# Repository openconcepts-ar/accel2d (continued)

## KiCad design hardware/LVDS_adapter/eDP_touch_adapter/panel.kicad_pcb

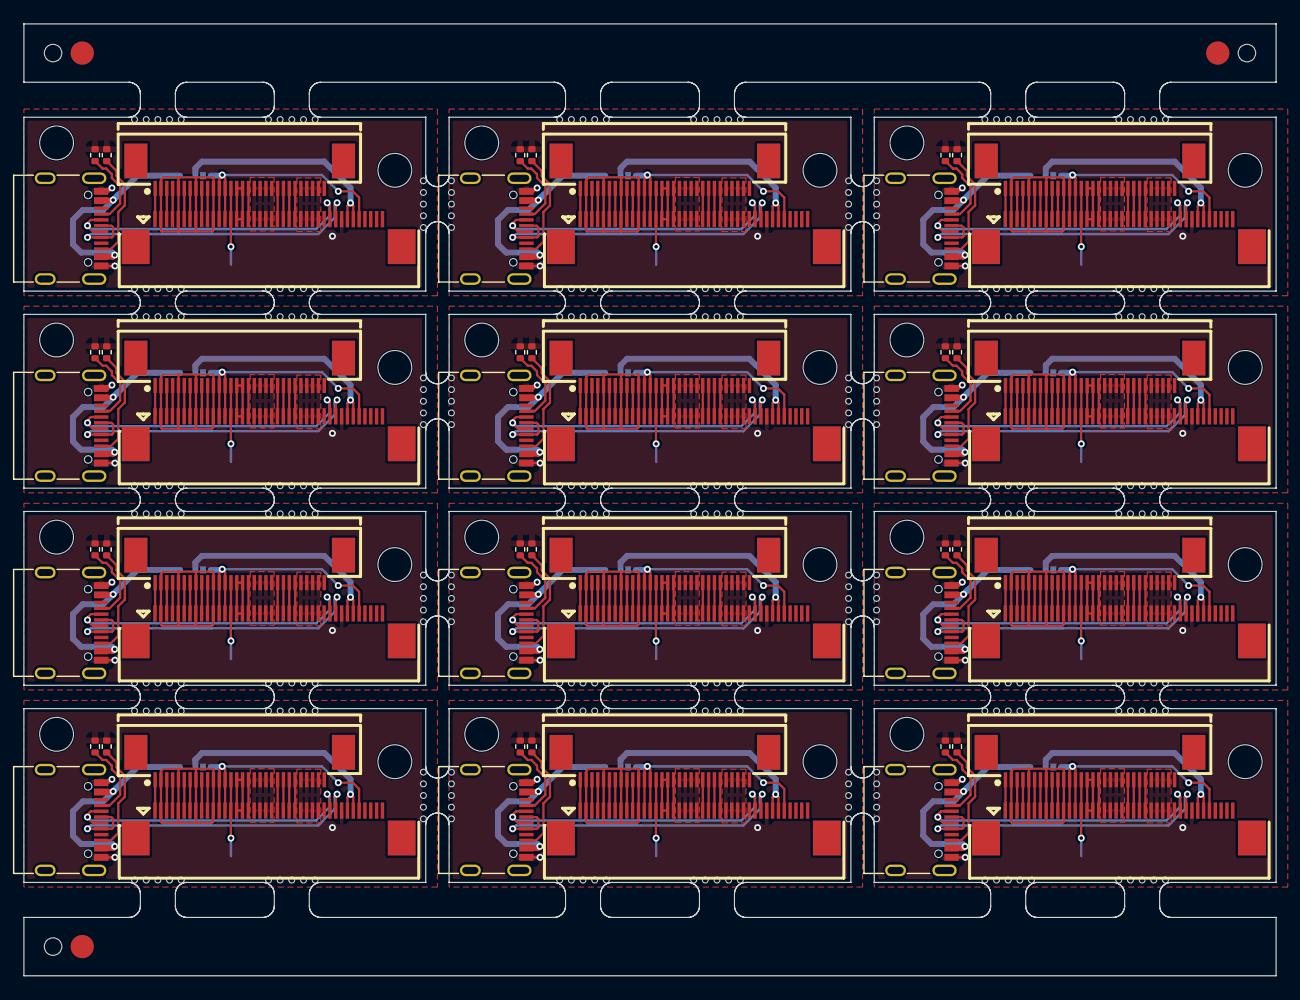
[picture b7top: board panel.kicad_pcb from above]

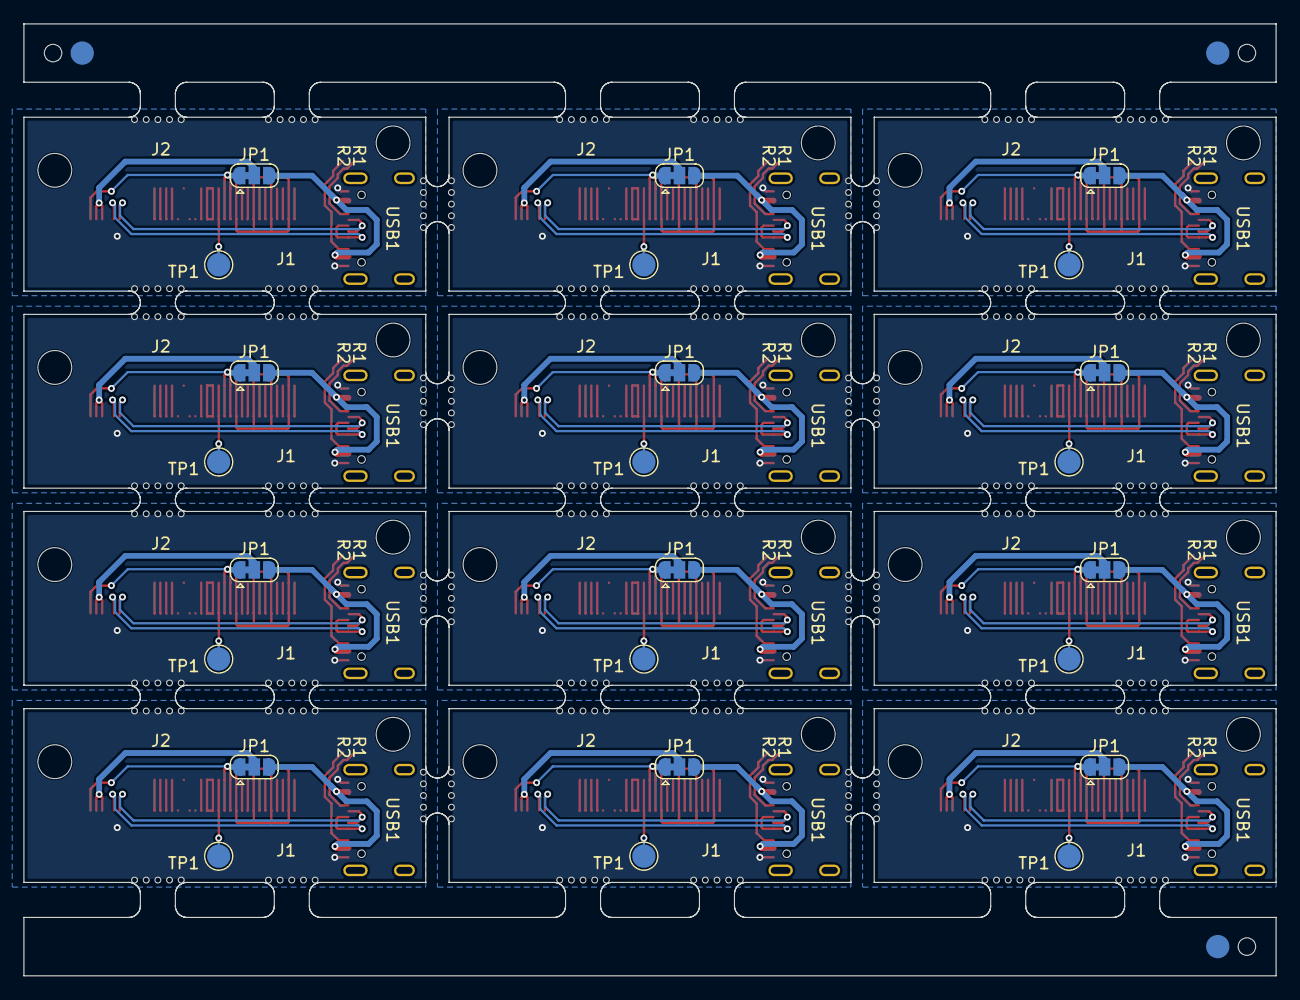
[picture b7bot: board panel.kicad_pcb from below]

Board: 2 copper layers, 107.4 x 81.6 mm, 437 parts (27 on the bottom side), 300 nets.

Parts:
H1, H1#2, H1#3, H1#4, H1#5, H1#6, H1#7, H1#8, H1#9, H1#10, H1#11, H1#12, H2, H2#2, H2#3, H2#4, H2#5, H2#6, H2#7, H2#8, H2#9, H2#10, H2#11, H2#12: MountingHole; MountingHole_2.2mm_M2_ISO7380
J1, J1#2, J1#3, J1#4, J1#5, J1#6, J1#7, J1#8, J1#9, J1#10, J1#11, J1#12: Conn_01x40; FPC-SMD_40P-P0.50_L4.4-W25.6
J2, J2#2, J2#3, J2#4, J2#5, J2#6, J2#7, J2#8, J2#9, J2#10, J2#11, J2#12: Conn_01x30; FPC-SMD_30P-P0.50_L4.4-W20.6
JP1, JP1#2, JP1#3, JP1#4, JP1#5, JP1#6, JP1#7, JP1#8, JP1#9, JP1#10, JP1#11, JP1#12: SolderJumper_3_Bridged12; SolderJumper-3_P1.3mm_Bridged12_RoundedPad1.0x1.5mm
KiKit_FID_B_1, KiKit_FID_B_2, KiKit_FID_B_3: Fiducial
KiKit_FID_T_1, KiKit_FID_T_2, KiKit_FID_T_3: Fiducial
KiKit_MB_1_1, KiKit_MB_1_2, KiKit_MB_1_3, KiKit_MB_1_4, KiKit_MB_1_5, KiKit_MB_2_1, KiKit_MB_2_2, KiKit_MB_2_3, KiKit_MB_2_4, KiKit_MB_2_5, KiKit_MB_3_1, KiKit_MB_3_2, KiKit_MB_3_3, KiKit_MB_3_4, KiKit_MB_3_5, KiKit_MB_4_1, KiKit_MB_4_2, KiKit_MB_4_3, KiKit_MB_4_4, KiKit_MB_4_5, KiKit_MB_5_1, KiKit_MB_5_2, KiKit_MB_5_3, KiKit_MB_5_4, KiKit_MB_5_5, KiKit_MB_6_1, KiKit_MB_6_2, KiKit_MB_6_3, KiKit_MB_6_4, KiKit_MB_6_5, KiKit_MB_7_1, KiKit_MB_7_2, KiKit_MB_7_3, KiKit_MB_7_4, KiKit_MB_7_5, KiKit_MB_8_1, KiKit_MB_8_2, KiKit_MB_8_3, KiKit_MB_8_4, KiKit_MB_8_5, KiKit_MB_9_1, KiKit_MB_9_2, KiKit_MB_9_3, KiKit_MB_9_4, KiKit_MB_9_5, KiKit_MB_10_1, KiKit_MB_10_2, KiKit_MB_10_3, KiKit_MB_10_4, KiKit_MB_10_5, KiKit_MB_11_1, KiKit_MB_11_2, KiKit_MB_11_3, KiKit_MB_11_4, KiKit_MB_11_5, KiKit_MB_12_1, KiKit_MB_12_2, KiKit_MB_12_3, KiKit_MB_12_4, KiKit_MB_12_5, KiKit_MB_13_1, KiKit_MB_13_2, KiKit_MB_13_3, KiKit_MB_13_4, KiKit_MB_13_5, KiKit_MB_14_1, KiKit_MB_14_2, KiKit_MB_14_3, KiKit_MB_14_4, KiKit_MB_14_5, KiKit_MB_15_1, KiKit_MB_15_2, KiKit_MB_15_3, KiKit_MB_15_4, KiKit_MB_15_5, KiKit_MB_16_1, KiKit_MB_16_2, KiKit_MB_16_3, KiKit_MB_16_4, KiKit_MB_16_5, KiKit_MB_17_1, KiKit_MB_17_2, KiKit_MB_17_3, KiKit_MB_17_4, KiKit_MB_17_5, KiKit_MB_18_1, KiKit_MB_18_2, KiKit_MB_18_3, KiKit_MB_18_4, KiKit_MB_18_5, KiKit_MB_19_1, KiKit_MB_19_2, KiKit_MB_19_3, KiKit_MB_19_4, KiKit_MB_19_5, KiKit_MB_20_1, KiKit_MB_20_2, KiKit_MB_20_3, KiKit_MB_20_4, KiKit_MB_20_5, KiKit_MB_21_1, KiKit_MB_21_2, KiKit_MB_21_3, KiKit_MB_21_4, KiKit_MB_21_5, KiKit_MB_22_1, KiKit_MB_22_2, KiKit_MB_22_3, KiKit_MB_22_4, KiKit_MB_22_5, KiKit_MB_23_1, KiKit_MB_23_2, KiKit_MB_23_3, KiKit_MB_23_4, KiKit_MB_23_5, KiKit_MB_24_1, KiKit_MB_24_2, KiKit_MB_24_3, KiKit_MB_24_4, KiKit_MB_24_5, KiKit_MB_25_1, KiKit_MB_25_2, KiKit_MB_25_3, KiKit_MB_25_4, KiKit_MB_25_5, KiKit_MB_26_1, KiKit_MB_26_2, KiKit_MB_26_3, KiKit_MB_26_4, KiKit_MB_26_5, KiKit_MB_27_1, KiKit_MB_27_2, KiKit_MB_27_3, KiKit_MB_27_4, KiKit_MB_27_5, KiKit_MB_28_1, KiKit_MB_28_2, KiKit_MB_28_3, KiKit_MB_28_4, KiKit_MB_28_5, KiKit_MB_29_1, KiKit_MB_29_2, KiKit_MB_29_3, KiKit_MB_29_4, KiKit_MB_29_5, KiKit_MB_30_1, KiKit_MB_30_2, KiKit_MB_30_3, KiKit_MB_30_4, KiKit_MB_30_5, KiKit_MB_31_1, KiKit_MB_31_2, KiKit_MB_31_3, KiKit_MB_31_4, KiKit_MB_31_5, KiKit_MB_32_1, KiKit_MB_32_2, KiKit_MB_32_3, KiKit_MB_32_4, KiKit_MB_32_5, KiKit_MB_33_1, KiKit_MB_33_2, KiKit_MB_33_3, KiKit_MB_33_4, KiKit_MB_33_5, KiKit_MB_34_1, KiKit_MB_34_2, KiKit_MB_34_3, KiKit_MB_34_4, KiKit_MB_34_5, KiKit_MB_35_1, KiKit_MB_35_2, KiKit_MB_35_3, KiKit_MB_35_4, KiKit_MB_35_5, KiKit_MB_36_1, KiKit_MB_36_2, KiKit_MB_36_3, KiKit_MB_36_4, KiKit_MB_36_5, KiKit_MB_37_1, KiKit_MB_37_2, KiKit_MB_37_3, KiKit_MB_37_4, KiKit_MB_37_5, KiKit_MB_38_1, KiKit_MB_38_2, KiKit_MB_38_3, KiKit_MB_38_4, KiKit_MB_38_5, KiKit_MB_39_1, KiKit_MB_39_2, KiKit_MB_39_3, KiKit_MB_39_4, KiKit_MB_39_5, KiKit_MB_40_1, KiKit_MB_40_2, KiKit_MB_40_3, KiKit_MB_40_4, KiKit_MB_40_5, KiKit_MB_41_1, KiKit_MB_41_2, KiKit_MB_41_3, KiKit_MB_41_4, KiKit_MB_41_5, KiKit_MB_42_1, KiKit_MB_42_2, KiKit_MB_42_3, KiKit_MB_42_4, KiKit_MB_42_5, KiKit_MB_43_1, KiKit_MB_43_2, KiKit_MB_43_3, KiKit_MB_43_4, KiKit_MB_43_5, KiKit_MB_44_1, KiKit_MB_44_2, KiKit_MB_44_3, KiKit_MB_44_4, KiKit_MB_44_5, KiKit_MB_45_1, KiKit_MB_45_2, KiKit_MB_45_3, KiKit_MB_45_4, KiKit_MB_45_5, KiKit_MB_46_1, KiKit_MB_46_2, KiKit_MB_46_3, KiKit_MB_46_4, KiKit_MB_46_5, KiKit_MB_47_1, KiKit_MB_47_2, KiKit_MB_47_3, KiKit_MB_47_4, KiKit_MB_47_5, KiKit_MB_48_1, KiKit_MB_48_2, KiKit_MB_48_3, KiKit_MB_48_4, KiKit_MB_48_5, KiKit_MB_49_1, KiKit_MB_49_2, KiKit_MB_49_3, KiKit_MB_49_4, KiKit_MB_49_5, KiKit_MB_50_1, KiKit_MB_50_2, KiKit_MB_50_3, KiKit_MB_50_4, KiKit_MB_50_5, KiKit_MB_51_1, KiKit_MB_51_2, KiKit_MB_51_3, KiKit_MB_51_4, KiKit_MB_51_5, KiKit_MB_52_1, KiKit_MB_52_2, KiKit_MB_52_3, KiKit_MB_52_4, KiKit_MB_52_5, KiKit_MB_53_1, KiKit_MB_53_2, KiKit_MB_53_3, KiKit_MB_53_4, KiKit_MB_53_5, KiKit_MB_54_1, KiKit_MB_54_2, KiKit_MB_54_3, KiKit_MB_54_4, KiKit_MB_54_5, KiKit_MB_55_1, KiKit_MB_55_2, KiKit_MB_55_3, KiKit_MB_55_4, KiKit_MB_55_5, KiKit_MB_56_1, KiKit_MB_56_2, KiKit_MB_56_3, KiKit_MB_56_4, KiKit_MB_56_5, KiKit_MB_57_1, KiKit_MB_57_2, KiKit_MB_57_3, KiKit_MB_57_4, KiKit_MB_57_5, KiKit_MB_58_1, KiKit_MB_58_2, KiKit_MB_58_3, KiKit_MB_58_4, KiKit_MB_58_5, KiKit_MB_59_1, KiKit_MB_59_2, KiKit_MB_59_3, KiKit_MB_59_4, KiKit_MB_59_5, KiKit_MB_60_1, KiKit_MB_60_2, KiKit_MB_60_3, KiKit_MB_60_4, KiKit_MB_60_5, KiKit_MB_61_1, KiKit_MB_61_2, KiKit_MB_61_3, KiKit_MB_61_4, KiKit_MB_61_5, KiKit_MB_62_1, KiKit_MB_62_2, KiKit_MB_62_3, KiKit_MB_62_4, KiKit_MB_62_5, KiKit_MB_63_1, KiKit_MB_63_2, KiKit_MB_63_3, KiKit_MB_63_4, KiKit_MB_63_5, KiKit_MB_64_1, KiKit_MB_64_2, KiKit_MB_64_3, KiKit_MB_64_4, KiKit_MB_64_5: NPTH
KiKit_TO_1, KiKit_TO_2, KiKit_TO_3: NPTH
R1, R1#2, R1#3, R1#4, R1#5, R1#6, R1#7, R1#8, R1#9, R1#10, R1#11, R1#12, R2, R2#2, R2#3, R2#4, R2#5, R2#6, R2#7, R2#8, R2#9, R2#10, R2#11, R2#12: 5.1k; R_0402_1005Metric
TP1, TP1#2, TP1#3, TP1#4, TP1#5, TP1#6, TP1#7, TP1#8, TP1#9, TP1#10, TP1#11, TP1#12: TestPoint_Small; TestPoint_Pad_D2.0mm
USB1, USB1#2, USB1#3, USB1#4, USB1#5, USB1#6, USB1#7, USB1#8, USB1#9, USB1#10, USB1#11, USB1#12: USB_C_Receptacle_USB2.0; USB_C_Receptacle_G-Switch_GT-USB-7010ASV

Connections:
Board_0-+3V3: J1#8.12, J1#8.13, J1#8.36, J2#6.12, J2#6.13, JP1#5.1 (A)
Board_0-+5V: JP1#5.3 (B), USB1#6.A4 (VBUS), USB1#6.A9 (VBUS), USB1#6.B4 (VBUS), USB1#6.B9 (VBUS)
Board_0-/AUX_N: J1#8.10, J2#6.10
Board_0-/AUX_P: J1#8.9, J2#6.9
Board_0-/BL_EN: J1#8.22, J2#6.22
Board_0-/BL_GND: J1#8.18, J1#8.19, J1#8.20, J1#8.21, J2#6.18, J2#6.19, J2#6.20, J2#6.21
Board_0-/BL_PWM: J1#8.23, J2#6.23
Board_0-/BL_PWR: J1#8.26, J1#8.27, J1#8.28, J1#8.29, J2#6.26, J2#6.27, J2#6.28, J2#6.29
Board_0-/EDP0_N: J1#8.6, J2#6.6
Board_0-/EDP1_N: J1#8.3, J2#6.3
Board_0-/EDP1_P: J1#8.4, J2#6.4
Board_0-/EDPO_P: J1#8.7, J2#6.7
Board_0-/HGND: J1#8.2, J1#8.5, J1#8.8, J1#8.11, J2#6.2, J2#6.5, J2#6.8, J2#6.11
Board_0-/HPD: J1#8.17, J2#6.17
Board_0-/LCD_GND: J1#8.15, J1#8.16, J2#6.15, J2#6.16
Board_0-/TEST: J1#8.14, J2#6.14, TP1#12.1
Board_0-/VTSP: J1#8.34, J1#8.35, JP1#5.2 (C)
Board_0-GND: J1#8.33, R1#6.2, R2#2.2, USB1#6.A1 (GND), USB1#6.A12 (GND), USB1#6.B1 (GND), USB1#6.B12 (GND)
Board_0-Net-(USB1-CC1): R1#6.1, USB1#6.A5 (CC1)
Board_0-Net-(USB1-CC2): R2#2.1, USB1#6.B5 (CC2)
Board_0-TP_D+: J1#8.32, USB1#6.A6 (D+), USB1#6.B6 (D+)
Board_0-TP_D-: J1#8.31, USB1#6.A7 (D-), USB1#6.B7 (D-)
Board_0-unconnected-(J1-Pin_1-Pad1): J1#8.1, J2#6.1
Board_0-unconnected-(J1-Pin_24-Pad24): J1#8.24, J2#6.24
Board_0-unconnected-(J1-Pin_25-Pad25): J1#8.25, J2#6.25
Board_1-+3V3: J1#9.12, J1#9.13, J1#9.36, J2#11.12, J2#11.13, JP1#10.1 (A)
Board_1-+5V: JP1#10.3 (B), USB1#10.A4 (VBUS), USB1#10.A9 (VBUS), USB1#10.B4 (VBUS), USB1#10.B9 (VBUS)
Board_1-/AUX_N: J1#9.10, J2#11.10
Board_1-/AUX_P: J1#9.9, J2#11.9
Board_1-/BL_EN: J1#9.22, J2#11.22
Board_1-/BL_GND: J1#9.18, J1#9.19, J1#9.20, J1#9.21, J2#11.18, J2#11.19, J2#11.20, J2#11.21
Board_1-/BL_PWM: J1#9.23, J2#11.23
Board_1-/BL_PWR: J1#9.26, J1#9.27, J1#9.28, J1#9.29, J2#11.26, J2#11.27, J2#11.28, J2#11.29
Board_1-/EDP0_N: J1#9.6, J2#11.6
Board_1-/EDP1_N: J1#9.3, J2#11.3
Board_1-/EDP1_P: J1#9.4, J2#11.4
Board_1-/EDPO_P: J1#9.7, J2#11.7
Board_1-/HGND: J1#9.2, J1#9.5, J1#9.8, J1#9.11, J2#11.2, J2#11.5, J2#11.8, J2#11.11
Board_1-/HPD: J1#9.17, J2#11.17
Board_1-/LCD_GND: J1#9.15, J1#9.16, J2#11.15, J2#11.16
Board_1-/TEST: J1#9.14, J2#11.14, TP1#9.1
Board_1-/VTSP: J1#9.34, J1#9.35, JP1#10.2 (C)
Board_1-GND: J1#9.33, R1#2.2, R2#6.2, USB1#10.A1 (GND), USB1#10.A12 (GND), USB1#10.B1 (GND), USB1#10.B12 (GND)
Board_1-Net-(USB1-CC1): R1#2.1, USB1#10.A5 (CC1)
Board_1-Net-(USB1-CC2): R2#6.1, USB1#10.B5 (CC2)
Board_1-TP_D+: J1#9.32, USB1#10.A6 (D+), USB1#10.B6 (D+)
Board_1-TP_D-: J1#9.31, USB1#10.A7 (D-), USB1#10.B7 (D-)
Board_1-unconnected-(J1-Pin_1-Pad1): J1#9.1, J2#11.1
Board_1-unconnected-(J1-Pin_24-Pad24): J1#9.24, J2#11.24
Board_1-unconnected-(J1-Pin_25-Pad25): J1#9.25, J2#11.25
Board_2-+3V3: J1#6.12, J1#6.13, J1#6.36, J2#9.12, J2#9.13, JP1#12.1 (A)
Board_2-+5V: JP1#12.3 (B), USB1#4.A4 (VBUS), USB1#4.A9 (VBUS), USB1#4.B4 (VBUS), USB1#4.B9 (VBUS)
Board_2-/AUX_N: J1#6.10, J2#9.10
Board_2-/AUX_P: J1#6.9, J2#9.9
Board_2-/BL_EN: J1#6.22, J2#9.22
Board_2-/BL_GND: J1#6.18, J1#6.19, J1#6.20, J1#6.21, J2#9.18, J2#9.19, J2#9.20, J2#9.21
Board_2-/BL_PWM: J1#6.23, J2#9.23
Board_2-/BL_PWR: J1#6.26, J1#6.27, J1#6.28, J1#6.29, J2#9.26, J2#9.27, J2#9.28, J2#9.29
Board_2-/EDP0_N: J1#6.6, J2#9.6
Board_2-/EDP1_N: J1#6.3, J2#9.3
Board_2-/EDP1_P: J1#6.4, J2#9.4
Board_2-/EDPO_P: J1#6.7, J2#9.7
Board_2-/HGND: J1#6.2, J1#6.5, J1#6.8, J1#6.11, J2#9.2, J2#9.5, J2#9.8, J2#9.11
Board_2-/HPD: J1#6.17, J2#9.17
Board_2-/LCD_GND: J1#6.15, J1#6.16, J2#9.15, J2#9.16
Board_2-/TEST: J1#6.14, J2#9.14, TP1#7.1
Board_2-/VTSP: J1#6.34, J1#6.35, JP1#12.2 (C)
Board_2-GND: J1#6.33, R1.2, R2#3.2, USB1#4.A1 (GND), USB1#4.A12 (GND), USB1#4.B1 (GND), USB1#4.B12 (GND)
Board_2-Net-(USB1-CC1): R1.1, USB1#4.A5 (CC1)
Board_2-Net-(USB1-CC2): R2#3.1, USB1#4.B5 (CC2)
Board_2-TP_D+: J1#6.32, USB1#4.A6 (D+), USB1#4.B6 (D+)
Board_2-TP_D-: J1#6.31, USB1#4.A7 (D-), USB1#4.B7 (D-)
Board_2-unconnected-(J1-Pin_1-Pad1): J1#6.1, J2#9.1
Board_2-unconnected-(J1-Pin_24-Pad24): J1#6.24, J2#9.24
Board_2-unconnected-(J1-Pin_25-Pad25): J1#6.25, J2#9.25
Board_3-+3V3: J1#12.12, J1#12.13, J1#12.36, J2.12, J2.13, JP1#4.1 (A)
Board_3-+5V: JP1#4.3 (B), USB1#3.A4 (VBUS), USB1#3.A9 (VBUS), USB1#3.B4 (VBUS), USB1#3.B9 (VBUS)
Board_3-/AUX_N: J1#12.10, J2.10
Board_3-/AUX_P: J1#12.9, J2.9
Board_3-/BL_EN: J1#12.22, J2.22
Board_3-/BL_GND: J1#12.18, J1#12.19, J1#12.20, J1#12.21, J2.18, J2.19, J2.20, J2.21
Board_3-/BL_PWM: J1#12.23, J2.23
Board_3-/BL_PWR: J1#12.26, J1#12.27, J1#12.28, J1#12.29, J2.26, J2.27, J2.28, J2.29
Board_3-/EDP0_N: J1#12.6, J2.6
Board_3-/EDP1_N: J1#12.3, J2.3
Board_3-/EDP1_P: J1#12.4, J2.4
Board_3-/EDPO_P: J1#12.7, J2.7
Board_3-/HGND: J1#12.2, J1#12.5, J1#12.8, J1#12.11, J2.2, J2.5, J2.8, J2.11
Board_3-/HPD: J1#12.17, J2.17
Board_3-/LCD_GND: J1#12.15, J1#12.16, J2.15, J2.16
Board_3-/TEST: J1#12.14, J2.14, TP1#8.1
Board_3-/VTSP: J1#12.34, J1#12.35, JP1#4.2 (C)
Board_3-GND: J1#12.33, R1#12.2, R2#10.2, USB1#3.A1 (GND), USB1#3.A12 (GND), USB1#3.B1 (GND), USB1#3.B12 (GND)
Board_3-Net-(USB1-CC1): R1#12.1, USB1#3.A5 (CC1)
Board_3-Net-(USB1-CC2): R2#10.1, USB1#3.B5 (CC2)
Board_3-TP_D+: J1#12.32, USB1#3.A6 (D+), USB1#3.B6 (D+)
Board_3-TP_D-: J1#12.31, USB1#3.A7 (D-), USB1#3.B7 (D-)
Board_3-unconnected-(J1-Pin_1-Pad1): J1#12.1, J2.1
Board_3-unconnected-(J1-Pin_24-Pad24): J1#12.24, J2.24
Board_3-unconnected-(J1-Pin_25-Pad25): J1#12.25, J2.25
Board_4-+3V3: J1#10.12, J1#10.13, J1#10.36, J2#8.12, J2#8.13, JP1#6.1 (A)
Board_4-+5V: JP1#6.3 (B), USB1#12.A4 (VBUS), USB1#12.A9 (VBUS), USB1#12.B4 (VBUS), USB1#12.B9 (VBUS)
Board_4-/AUX_N: J1#10.10, J2#8.10
Board_4-/AUX_P: J1#10.9, J2#8.9
Board_4-/BL_EN: J1#10.22, J2#8.22
Board_4-/BL_GND: J1#10.18, J1#10.19, J1#10.20, J1#10.21, J2#8.18, J2#8.19, J2#8.20, J2#8.21
Board_4-/BL_PWM: J1#10.23, J2#8.23
Board_4-/BL_PWR: J1#10.26, J1#10.27, J1#10.28, J1#10.29, J2#8.26, J2#8.27, J2#8.28, J2#8.29
Board_4-/EDP0_N: J1#10.6, J2#8.6
Board_4-/EDP1_N: J1#10.3, J2#8.3
Board_4-/EDP1_P: J1#10.4, J2#8.4
Board_4-/EDPO_P: J1#10.7, J2#8.7
Board_4-/HGND: J1#10.2, J1#10.5, J1#10.8, J1#10.11, J2#8.2, J2#8.5, J2#8.8, J2#8.11
Board_4-/HPD: J1#10.17, J2#8.17
Board_4-/LCD_GND: J1#10.15, J1#10.16, J2#8.15, J2#8.16
Board_4-/TEST: J1#10.14, J2#8.14, TP1#11.1
Board_4-/VTSP: J1#10.34, J1#10.35, JP1#6.2 (C)
Board_4-GND: J1#10.33, R1#3.2, R2#5.2, USB1#12.A1 (GND), USB1#12.A12 (GND), USB1#12.B1 (GND), USB1#12.B12 (GND)
Board_4-Net-(USB1-CC1): R1#3.1, USB1#12.A5 (CC1)
Board_4-Net-(USB1-CC2): R2#5.1, USB1#12.B5 (CC2)
Board_4-TP_D+: J1#10.32, USB1#12.A6 (D+), USB1#12.B6 (D+)
Board_4-TP_D-: J1#10.31, USB1#12.A7 (D-), USB1#12.B7 (D-)
Board_4-unconnected-(J1-Pin_1-Pad1): J1#10.1, J2#8.1
Board_4-unconnected-(J1-Pin_24-Pad24): J1#10.24, J2#8.24
Board_4-unconnected-(J1-Pin_25-Pad25): J1#10.25, J2#8.25
Board_5-+3V3: J1#7.12, J1#7.13, J1#7.36, J2#3.12, J2#3.13, JP1#9.1 (A)
Board_5-+5V: JP1#9.3 (B), USB1#8.A4 (VBUS), USB1#8.A9 (VBUS), USB1#8.B4 (VBUS), USB1#8.B9 (VBUS)
Board_5-/AUX_N: J1#7.10, J2#3.10
Board_5-/AUX_P: J1#7.9, J2#3.9
Board_5-/BL_EN: J1#7.22, J2#3.22
Board_5-/BL_GND: J1#7.18, J1#7.19, J1#7.20, J1#7.21, J2#3.18, J2#3.19, J2#3.20, J2#3.21
Board_5-/BL_PWM: J1#7.23, J2#3.23
Board_5-/BL_PWR: J1#7.26, J1#7.27, J1#7.28, J1#7.29, J2#3.26, J2#3.27, J2#3.28, J2#3.29
Board_5-/EDP0_N: J1#7.6, J2#3.6
Board_5-/EDP1_N: J1#7.3, J2#3.3
Board_5-/EDP1_P: J1#7.4, J2#3.4
Board_5-/EDPO_P: J1#7.7, J2#3.7
Board_5-/HGND: J1#7.2, J1#7.5, J1#7.8, J1#7.11, J2#3.2, J2#3.5, J2#3.8, J2#3.11
Board_5-/HPD: J1#7.17, J2#3.17
Board_5-/LCD_GND: J1#7.15, J1#7.16, J2#3.15, J2#3.16
Board_5-/TEST: J1#7.14, J2#3.14, TP1#10.1
Board_5-/VTSP: J1#7.34, J1#7.35, JP1#9.2 (C)
Board_5-GND: J1#7.33, R1#4.2, R2#11.2, USB1#8.A1 (GND), USB1#8.A12 (GND), USB1#8.B1 (GND), USB1#8.B12 (GND)
Board_5-Net-(USB1-CC1): R1#4.1, USB1#8.A5 (CC1)
Board_5-Net-(USB1-CC2): R2#11.1, USB1#8.B5 (CC2)
Board_5-TP_D+: J1#7.32, USB1#8.A6 (D+), USB1#8.B6 (D+)
Board_5-TP_D-: J1#7.31, USB1#8.A7 (D-), USB1#8.B7 (D-)
Board_5-unconnected-(J1-Pin_1-Pad1): J1#7.1, J2#3.1
Board_5-unconnected-(J1-Pin_24-Pad24): J1#7.24, J2#3.24
Board_5-unconnected-(J1-Pin_25-Pad25): J1#7.25, J2#3.25
Board_6-+3V3: J1.12, J1.13, J1.36, J2#2.12, J2#2.13, JP1.1 (A)
Board_6-+5V: JP1.3 (B), USB1#7.A4 (VBUS), USB1#7.A9 (VBUS), USB1#7.B4 (VBUS), USB1#7.B9 (VBUS)
Board_6-/AUX_N: J1.10, J2#2.10
Board_6-/AUX_P: J1.9, J2#2.9
Board_6-/BL_EN: J1.22, J2#2.22
Board_6-/BL_GND: J1.18, J1.19, J1.20, J1.21, J2#2.18, J2#2.19, J2#2.20, J2#2.21
Board_6-/BL_PWM: J1.23, J2#2.23
Board_6-/BL_PWR: J1.26, J1.27, J1.28, J1.29, J2#2.26, J2#2.27, J2#2.28, J2#2.29
Board_6-/EDP0_N: J1.6, J2#2.6
Board_6-/EDP1_N: J1.3, J2#2.3
Board_6-/EDP1_P: J1.4, J2#2.4
Board_6-/EDPO_P: J1.7, J2#2.7
Board_6-/HGND: J1.2, J1.5, J1.8, J1.11, J2#2.2, J2#2.5, J2#2.8, J2#2.11
Board_6-/HPD: J1.17, J2#2.17
Board_6-/LCD_GND: J1.15, J1.16, J2#2.15, J2#2.16
Board_6-/TEST: J1.14, J2#2.14, TP1#6.1
Board_6-/VTSP: J1.34, J1.35, JP1.2 (C)
Board_6-GND: J1.33, R1#7.2, R2#4.2, USB1#7.A1 (GND), USB1#7.A12 (GND), USB1#7.B1 (GND), USB1#7.B12 (GND)
Board_6-Net-(USB1-CC1): R1#7.1, USB1#7.A5 (CC1)
Board_6-Net-(USB1-CC2): R2#4.1, USB1#7.B5 (CC2)
Board_6-TP_D+: J1.32, USB1#7.A6 (D+), USB1#7.B6 (D+)
Board_6-TP_D-: J1.31, USB1#7.A7 (D-), USB1#7.B7 (D-)
Board_6-unconnected-(J1-Pin_1-Pad1): J1.1, J2#2.1
Board_6-unconnected-(J1-Pin_24-Pad24): J1.24, J2#2.24
Board_6-unconnected-(J1-Pin_25-Pad25): J1.25, J2#2.25
Board_7-+3V3: J1#11.12, J1#11.13, J1#11.36, J2#4.12, J2#4.13, JP1#3.1 (A)
Board_7-+5V: JP1#3.3 (B), USB1#9.A4 (VBUS), USB1#9.A9 (VBUS), USB1#9.B4 (VBUS), USB1#9.B9 (VBUS)
Board_7-/AUX_N: J1#11.10, J2#4.10
Board_7-/AUX_P: J1#11.9, J2#4.9
Board_7-/BL_EN: J1#11.22, J2#4.22
Board_7-/BL_GND: J1#11.18, J1#11.19, J1#11.20, J1#11.21, J2#4.18, J2#4.19, J2#4.20, J2#4.21
Board_7-/BL_PWM: J1#11.23, J2#4.23
Board_7-/BL_PWR: J1#11.26, J1#11.27, J1#11.28, J1#11.29, J2#4.26, J2#4.27, J2#4.28, J2#4.29
Board_7-/EDP0_N: J1#11.6, J2#4.6
Board_7-/EDP1_N: J1#11.3, J2#4.3
Board_7-/EDP1_P: J1#11.4, J2#4.4
Board_7-/EDPO_P: J1#11.7, J2#4.7
Board_7-/HGND: J1#11.2, J1#11.5, J1#11.8, J1#11.11, J2#4.2, J2#4.5, J2#4.8, J2#4.11
Board_7-/HPD: J1#11.17, J2#4.17
Board_7-/LCD_GND: J1#11.15, J1#11.16, J2#4.15, J2#4.16
Board_7-/TEST: J1#11.14, J2#4.14, TP1.1
Board_7-/VTSP: J1#11.34, J1#11.35, JP1#3.2 (C)
Board_7-GND: J1#11.33, R1#10.2, R2#7.2, USB1#9.A1 (GND), USB1#9.A12 (GND), USB1#9.B1 (GND), USB1#9.B12 (GND)
Board_7-Net-(USB1-CC1): R1#10.1, USB1#9.A5 (CC1)
Board_7-Net-(USB1-CC2): R2#7.1, USB1#9.B5 (CC2)
Board_7-TP_D+: J1#11.32, USB1#9.A6 (D+), USB1#9.B6 (D+)
Board_7-TP_D-: J1#11.31, USB1#9.A7 (D-), USB1#9.B7 (D-)
Board_7-unconnected-(J1-Pin_1-Pad1): J1#11.1, J2#4.1
Board_7-unconnected-(J1-Pin_24-Pad24): J1#11.24, J2#4.24
Board_7-unconnected-(J1-Pin_25-Pad25): J1#11.25, J2#4.25
Board_8-+3V3: J1#5.12, J1#5.13, J1#5.36, J2#5.12, J2#5.13, JP1#11.1 (A)
Board_8-+5V: JP1#11.3 (B), USB1#2.A4 (VBUS), USB1#2.A9 (VBUS), USB1#2.B4 (VBUS), USB1#2.B9 (VBUS)
Board_8-/AUX_N: J1#5.10, J2#5.10
Board_8-/AUX_P: J1#5.9, J2#5.9
Board_8-/BL_EN: J1#5.22, J2#5.22
Board_8-/BL_GND: J1#5.18, J1#5.19, J1#5.20, J1#5.21, J2#5.18, J2#5.19, J2#5.20, J2#5.21
Board_8-/BL_PWM: J1#5.23, J2#5.23
Board_8-/BL_PWR: J1#5.26, J1#5.27, J1#5.28, J1#5.29, J2#5.26, J2#5.27, J2#5.28, J2#5.29
Board_8-/EDP0_N: J1#5.6, J2#5.6
Board_8-/EDP1_N: J1#5.3, J2#5.3
Board_8-/EDP1_P: J1#5.4, J2#5.4
Board_8-/EDPO_P: J1#5.7, J2#5.7
Board_8-/HGND: J1#5.2, J1#5.5, J1#5.8, J1#5.11, J2#5.2, J2#5.5, J2#5.8, J2#5.11
Board_8-/HPD: J1#5.17, J2#5.17
Board_8-/LCD_GND: J1#5.15, J1#5.16, J2#5.15, J2#5.16
Board_8-/TEST: J1#5.14, J2#5.14, TP1#5.1
Board_8-/VTSP: J1#5.34, J1#5.35, JP1#11.2 (C)
Board_8-GND: J1#5.33, R1#8.2, R2#8.2, USB1#2.A1 (GND), USB1#2.A12 (GND), USB1#2.B1 (GND), USB1#2.B12 (GND)
Board_8-Net-(USB1-CC1): R1#8.1, USB1#2.A5 (CC1)
Board_8-Net-(USB1-CC2): R2#8.1, USB1#2.B5 (CC2)
Board_8-TP_D+: J1#5.32, USB1#2.A6 (D+), USB1#2.B6 (D+)
Board_8-TP_D-: J1#5.31, USB1#2.A7 (D-), USB1#2.B7 (D-)
Board_8-unconnected-(J1-Pin_1-Pad1): J1#5.1, J2#5.1
Board_8-unconnected-(J1-Pin_24-Pad24): J1#5.24, J2#5.24
Board_8-unconnected-(J1-Pin_25-Pad25): J1#5.25, J2#5.25
Board_9-+3V3: J1#2.12, J1#2.13, J1#2.36, J2#10.12, J2#10.13, JP1#8.1 (A)
Board_9-+5V: JP1#8.3 (B), USB1#5.A4 (VBUS), USB1#5.A9 (VBUS), USB1#5.B4 (VBUS), USB1#5.B9 (VBUS)
Board_9-/AUX_N: J1#2.10, J2#10.10
Board_9-/AUX_P: J1#2.9, J2#10.9
Board_9-/BL_EN: J1#2.22, J2#10.22
Board_9-/BL_GND: J1#2.18, J1#2.19, J1#2.20, J1#2.21, J2#10.18, J2#10.19, J2#10.20, J2#10.21
Board_9-/BL_PWM: J1#2.23, J2#10.23
Board_9-/BL_PWR: J1#2.26, J1#2.27, J1#2.28, J1#2.29, J2#10.26, J2#10.27, J2#10.28, J2#10.29
Board_9-/EDP0_N: J1#2.6, J2#10.6
Board_9-/EDP1_N: J1#2.3, J2#10.3
Board_9-/EDP1_P: J1#2.4, J2#10.4
Board_9-/EDPO_P: J1#2.7, J2#10.7
Board_9-/HGND: J1#2.2, J1#2.5, J1#2.8, J1#2.11, J2#10.2, J2#10.5, J2#10.8, J2#10.11
Board_9-/HPD: J1#2.17, J2#10.17
Board_9-/LCD_GND: J1#2.15, J1#2.16, J2#10.15, J2#10.16
Board_9-/TEST: J1#2.14, J2#10.14, TP1#4.1
Board_9-/VTSP: J1#2.34, J1#2.35, JP1#8.2 (C)
Board_9-GND: J1#2.33, R1#5.2, R2#12.2, USB1#5.A1 (GND), USB1#5.A12 (GND), USB1#5.B1 (GND), USB1#5.B12 (GND)
Board_9-Net-(USB1-CC1): R1#5.1, USB1#5.A5 (CC1)
Board_9-Net-(USB1-CC2): R2#12.1, USB1#5.B5 (CC2)
Board_9-TP_D+: J1#2.32, USB1#5.A6 (D+), USB1#5.B6 (D+)
Board_9-TP_D-: J1#2.31, USB1#5.A7 (D-), USB1#5.B7 (D-)
Board_9-unconnected-(J1-Pin_1-Pad1): J1#2.1, J2#10.1
Board_9-unconnected-(J1-Pin_24-Pad24): J1#2.24, J2#10.24
Board_9-unconnected-(J1-Pin_25-Pad25): J1#2.25, J2#10.25
Board_10-+3V3: J1#4.12, J1#4.13, J1#4.36, J2#12.12, J2#12.13, JP1#7.1 (A)
Board_10-+5V: JP1#7.3 (B), USB1#11.A4 (VBUS), USB1#11.A9 (VBUS), USB1#11.B4 (VBUS), USB1#11.B9 (VBUS)
Board_10-/AUX_N: J1#4.10, J2#12.10
Board_10-/AUX_P: J1#4.9, J2#12.9
Board_10-/BL_EN: J1#4.22, J2#12.22
Board_10-/BL_GND: J1#4.18, J1#4.19, J1#4.20, J1#4.21, J2#12.18, J2#12.19, J2#12.20, J2#12.21
Board_10-/BL_PWM: J1#4.23, J2#12.23
Board_10-/BL_PWR: J1#4.26, J1#4.27, J1#4.28, J1#4.29, J2#12.26, J2#12.27, J2#12.28, J2#12.29
Board_10-/EDP0_N: J1#4.6, J2#12.6
Board_10-/EDP1_N: J1#4.3, J2#12.3
Board_10-/EDP1_P: J1#4.4, J2#12.4
Board_10-/EDPO_P: J1#4.7, J2#12.7
Board_10-/HGND: J1#4.2, J1#4.5, J1#4.8, J1#4.11, J2#12.2, J2#12.5, J2#12.8, J2#12.11
Board_10-/HPD: J1#4.17, J2#12.17
Board_10-/LCD_GND: J1#4.15, J1#4.16, J2#12.15, J2#12.16
Board_10-/TEST: J1#4.14, J2#12.14, TP1#3.1
Board_10-/VTSP: J1#4.34, J1#4.35, JP1#7.2 (C)
Board_10-GND: J1#4.33, R1#11.2, R2.2, USB1#11.A1 (GND), USB1#11.A12 (GND), USB1#11.B1 (GND), USB1#11.B12 (GND)
Board_10-Net-(USB1-CC1): R1#11.1, USB1#11.A5 (CC1)
Board_10-Net-(USB1-CC2): R2.1, USB1#11.B5 (CC2)
Board_10-TP_D+: J1#4.32, USB1#11.A6 (D+), USB1#11.B6 (D+)
Board_10-TP_D-: J1#4.31, USB1#11.A7 (D-), USB1#11.B7 (D-)
Board_10-unconnected-(J1-Pin_1-Pad1): J1#4.1, J2#12.1
Board_10-unconnected-(J1-Pin_24-Pad24): J1#4.24, J2#12.24
Board_10-unconnected-(J1-Pin_25-Pad25): J1#4.25, J2#12.25
Board_11-+3V3: J1#3.12, J1#3.13, J1#3.36, J2#7.12, J2#7.13, JP1#2.1 (A)
Board_11-+5V: JP1#2.3 (B), USB1.A4 (VBUS), USB1.A9 (VBUS), USB1.B4 (VBUS), USB1.B9 (VBUS)
Board_11-/AUX_N: J1#3.10, J2#7.10
Board_11-/AUX_P: J1#3.9, J2#7.9
Board_11-/BL_EN: J1#3.22, J2#7.22
Board_11-/BL_GND: J1#3.18, J1#3.19, J1#3.20, J1#3.21, J2#7.18, J2#7.19, J2#7.20, J2#7.21
Board_11-/BL_PWM: J1#3.23, J2#7.23
Board_11-/BL_PWR: J1#3.26, J1#3.27, J1#3.28, J1#3.29, J2#7.26, J2#7.27, J2#7.28, J2#7.29
Board_11-/EDP0_N: J1#3.6, J2#7.6
Board_11-/EDP1_N: J1#3.3, J2#7.3
Board_11-/EDP1_P: J1#3.4, J2#7.4
Board_11-/EDPO_P: J1#3.7, J2#7.7
Board_11-/HGND: J1#3.2, J1#3.5, J1#3.8, J1#3.11, J2#7.2, J2#7.5, J2#7.8, J2#7.11
Board_11-/HPD: J1#3.17, J2#7.17
Board_11-/LCD_GND: J1#3.15, J1#3.16, J2#7.15, J2#7.16
Board_11-/TEST: J1#3.14, J2#7.14, TP1#2.1
Board_11-/VTSP: J1#3.34, J1#3.35, JP1#2.2 (C)
Board_11-GND: J1#3.33, R1#9.2, R2#9.2, USB1.A1 (GND), USB1.A12 (GND), USB1.B1 (GND), USB1.B12 (GND)
Board_11-Net-(USB1-CC1): R1#9.1, USB1.A5 (CC1)
Board_11-Net-(USB1-CC2): R2#9.1, USB1.B5 (CC2)
Board_11-TP_D+: J1#3.32, USB1.A6 (D+), USB1.B6 (D+)
Board_11-TP_D-: J1#3.31, USB1.A7 (D-), USB1.B7 (D-)
Board_11-unconnected-(J1-Pin_1-Pad1): J1#3.1, J2#7.1
Board_11-unconnected-(J1-Pin_24-Pad24): J1#3.24, J2#7.24
Board_11-unconnected-(J1-Pin_25-Pad25): J1#3.25, J2#7.25
